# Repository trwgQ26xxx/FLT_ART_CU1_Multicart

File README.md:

# Multicart ROM module for Fiat Lancia Tester \ Alfa Romeo Tester \ Check Up 1

A multicart ROM module that replaces eight standard FLT modules. It contains eight ROM sets stored in a 512kB (4Mbit) flash memory, which can be switched on the fly.

Two variants are implemented: one using an Atmel AT89C2051 MCU (revisions A - green and B - blue), and another based on a Microchip ATtiny806 (revision C - yellow).

# Disclaimer

I do not consent to the use of all or part of the project for commercial purposes!

Nie wyrażam zgody na wykorzystanie całości bądź części projektu w celach zarobkowych!

# License

Shield: [![CC BY-NC-SA 4.0][cc-by-nc-sa-shield]][cc-by-nc-sa]

This work is licensed under a
[Creative Commons Attribution-NonCommercial-ShareAlike 4.0 International License][cc-by-nc-sa].

[![CC BY-NC-SA 4.0][cc-by-nc-sa-image]][cc-by-nc-sa]

[cc-by-nc-sa]: http://creativecommons.org/licenses/by-nc-sa/4.0/
[cc-by-nc-sa-image]: https://licensebuttons.net/l/by-nc-sa/4.0/88x31.png
[cc-by-nc-sa-shield]: https://img.shields.io/badge/License-CC%20BY--NC--SA%204.0-lightgrey.svg

# Directories organization

- **firmware** - MCU firmware written in C, provided for both the AT89C2051 and ATtiny806 variants.
- **merge** - A script that automatically combines up to eight modules into a single package suitable for loading onto the multicart.
- **PCB** - KiCad PCB project files, available for both the AT89C2051 and ATtiny806 hardware revisions.
- **DS** - Datasheets for all components used in the project.

# Instructions

Switching modules (ROMs) is accomplished by pressing the BACK and NEXT keys. With each press, a dot lights up on the display for the FLT reset time (approximately 200 ms). The display indicates the number of the currently running module.

The FLASH memories used, of 39SF040 type (or equivalent), have a capacity of 512kB. Considering that the largest FLT modules ROMs are 64kB, I designed the multicart's capacity to accomodate 8 modules.

# ROMS preparation

The FLASH memory contents can be changed according to the following principles.

**ROM index** | **Base offset**
:---: | :---:
1 | 0x00000
2 | 0x10000
3 | 0x20000
4 | 0x30000
5 | 0x40000
6 | 0x50000
7 | 0x60000
8 | 0x70000

Let's assume we want to load the module at index 3, for which the base offset is 0x20000.

**ROM** | **SIZE** | **The ROM given is PRESENT in the module being loaded at index 3** | **The ROM given is NOT PRESENT in the module being loaded at index 3**
:---: | :---: | :---: | :---:
A | 8kB | Load the content of ROM A into FLASH memory A addresses 0x20000-0x21FFF.Fill addresses 0x22000-0x2FFFF of FLASH memory A with 0xFF. | Fill addresses 0x20000-0x2FFFF of FLASH memory A with 0xFF.
B | 32kB | Load the content of ROM B into FLASH memory B addresses 0x28000-0x2FFFF. Fill addresses 0x20000-0x27FFF of FLASH memory B with 0xFF. | ROM B is always present.
B | 64kB | Load the content of ROM B into FLASH memory B addresses 0x20000-0x2FFFF. | ROM B is always present.
C | 32kB | Load the content of ROM C into FLASH memory C addresses 0x28000-0x2FFFF. Fill addresses 0x20000-0x27FFF of FLASH memory C with 0xFF. | Fill addresses 0x20000-0x2FFFF of FLASH memory C with 0xFF.
C | 64kB | Load the content of ROM C into FLASH memory C addresses 0x20000-0x2FFFF. | Fill addresses 0x20000-0x2FFFF of FLASH memory C with 0xFF.

It should be noted here that the utilization of FLASH memory A is at most 12.5%, as only 8kB of each 64kB bank is utilized. However, I opted for this solution to simplify the process of preparing Flash memory content, given the use of identical offsets.

# Notes

- Use the APX810-40SA as the reset supervisor for the AT89C2051 MCU (U7 on the PCB) in revisions A and B.

- Wiring the MPLAB ICD5 8P8C Connector to the Multicart PROG Connector (Revision C):

**SIGNAL** | **PROG pin** | **8P8C pin**
:---: | :---: | :---:
GND | 1 | 5
UPDI | 2 | 4
VCC | 3 | 6

- 0.28" LED displays are available in two pinout variants. The first variant uses common pins 1 and 6. The second variant uses common pins 3 and 8. **Revisions B and C of the project require the display with common pins 3 and 8.** The version with common pins 1 and 6 was used only in revision A.

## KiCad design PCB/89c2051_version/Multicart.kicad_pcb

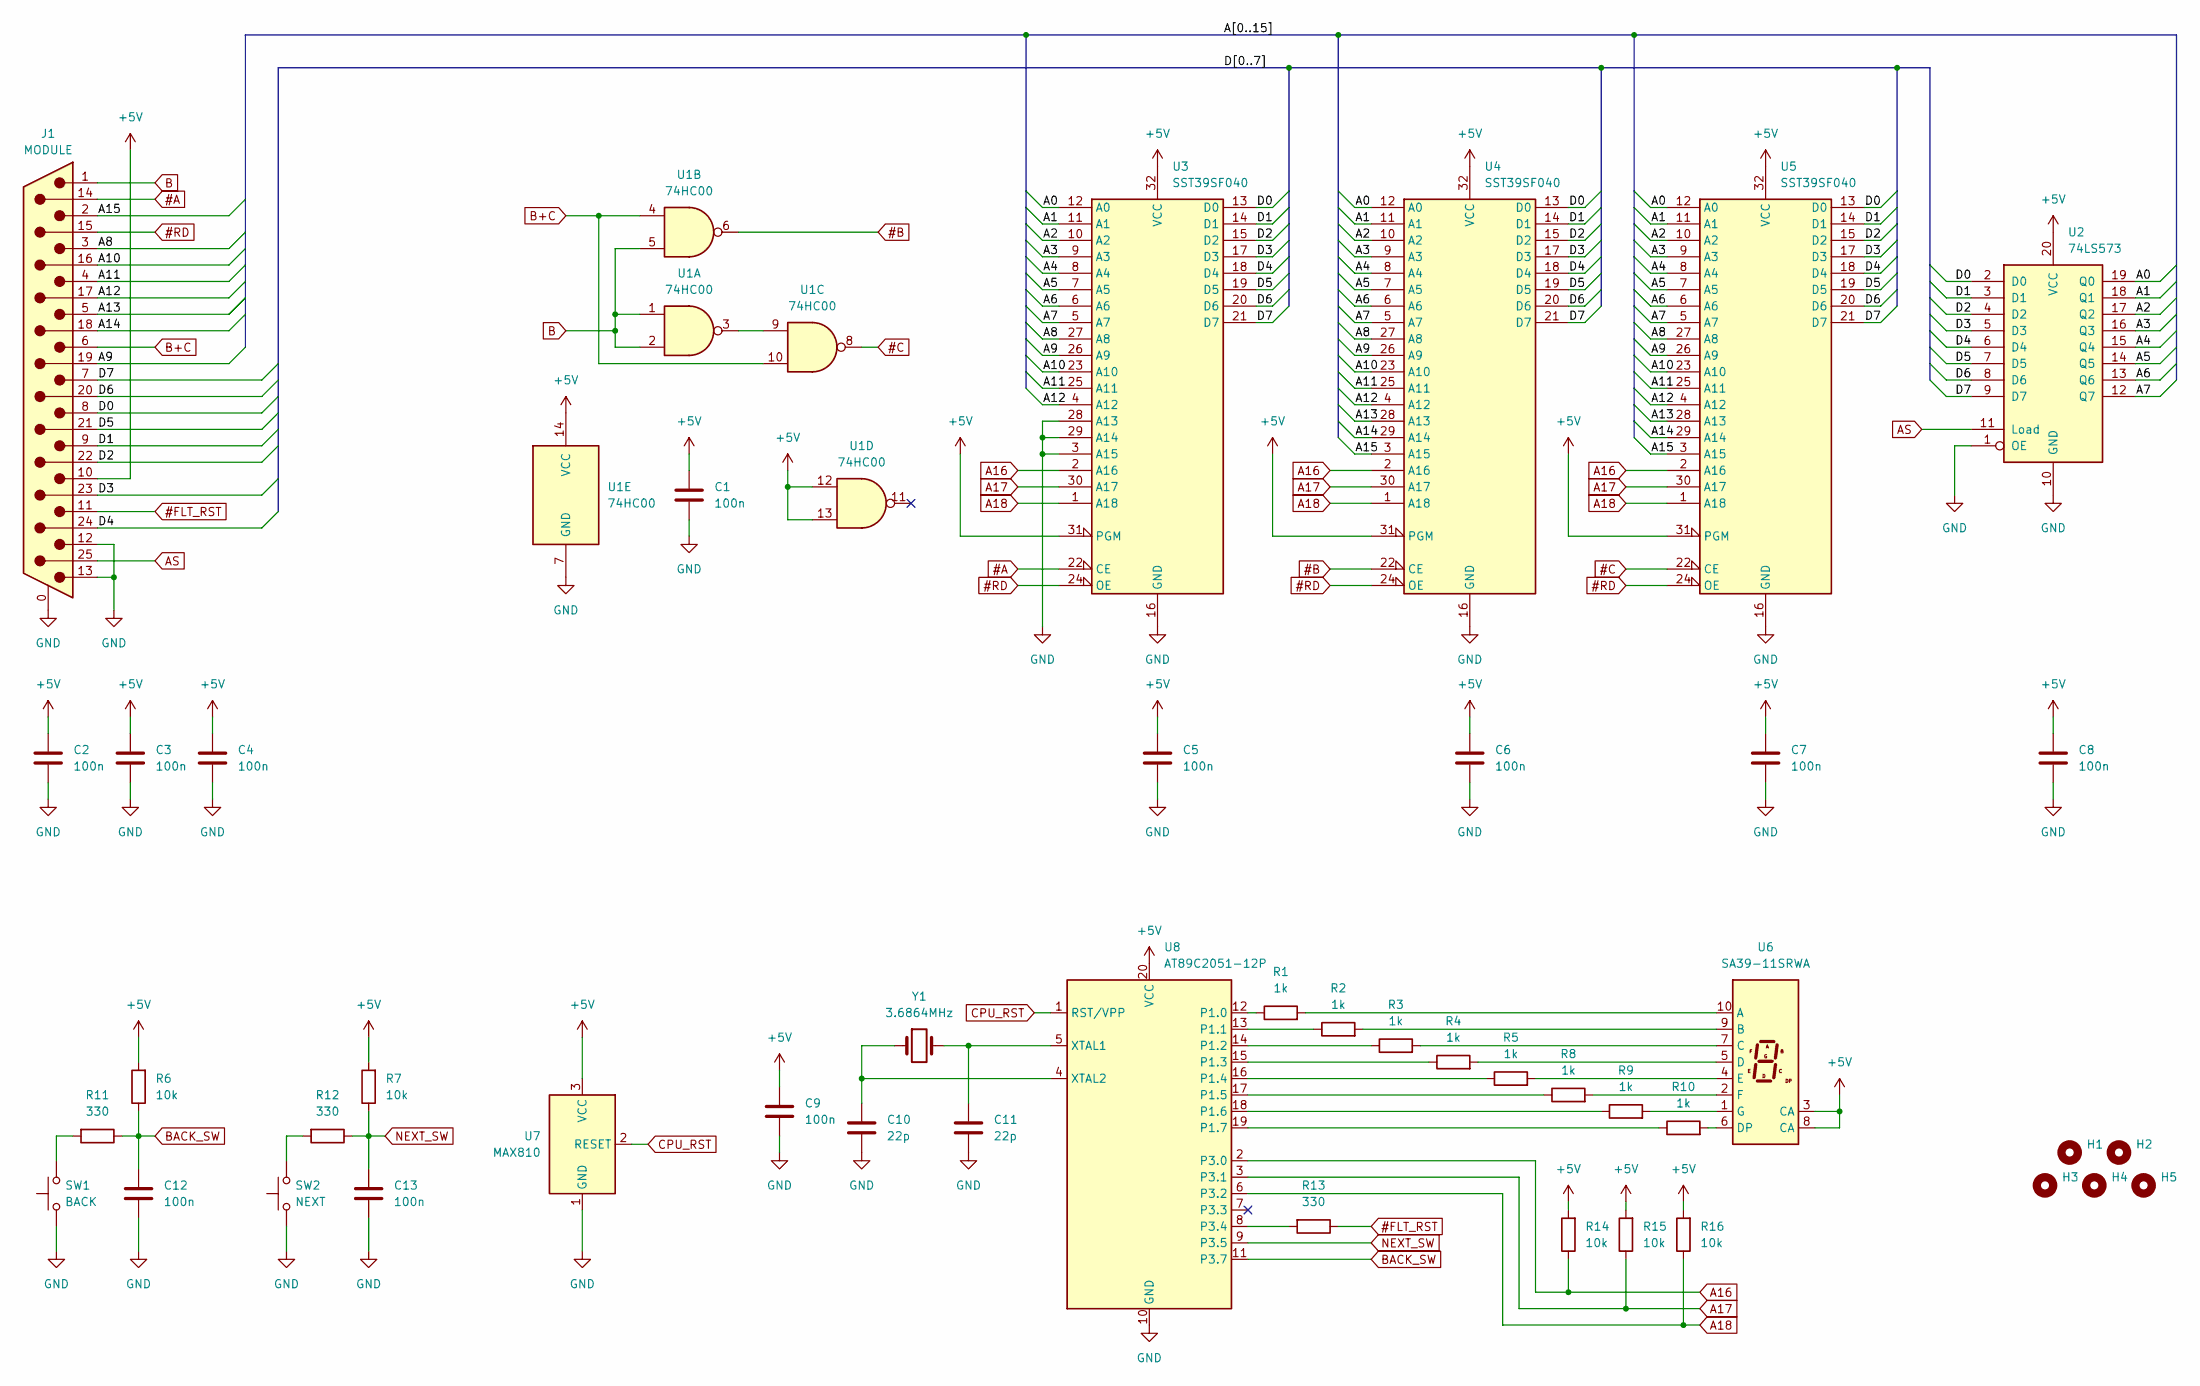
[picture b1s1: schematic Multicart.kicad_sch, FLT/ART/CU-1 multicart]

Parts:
C1, C2, C3, C4, C5, C6, C7, C8, C9, C12, C13: 100n; C_1206_3216Metric_Pad1.33x1.80mm_HandSolder
C10, C11: 22p; C_1206_3216Metric_Pad1.33x1.80mm_HandSolder
H1, H2, H3, H4, H5: MountingHole_3.2mm_M3_DIN965
J1: MODULE; DSUB-25_Male_Horizontal_P2.77x2.84mm_EdgePinOffset4.94mm_Ho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
R1, R2, R3, R4, R5, R8, R9, R10: 1k; R_1206_3216Metric_Pad1.30x1.75mm_HandSolder
R6, R7, R14, R15, R16: 10k; R_1206_3216Metric_Pad1.30x1.75mm_HandSolder
R11, R12, R13: 330; R_1206_3216Metric_Pad1.30x1.75mm_HandSolder
SW1: BACK; SW_PUSH_6mm
SW2: NEXT; SW_PUSH_6mm
U1: 74HC00; SOIC-14_3.9x8.7mm_P1.27mm
U2: 74LS573; SOIC-20W_7.5x12.8mm_P1.27mm
U3, U4, U5: SST39SF040; PLCC-32_11.4x14.0mm_P1.27mm
U6: SA39-11SRWA; Sx39-1xxxxx
U7: MAX810; SOT-23
U8: AT89C2051-12P; DIP-20_W7.62mm
Y1: 3.6864MHz; Crystal_HC49-4H_Vertical

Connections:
#A: J1.14, U3.22 (CE)
#B: U1.6, U4.22 (CE)
#C: U1.8, U5.22 (CE)
#FLT_RST: J1.11, R13.1
#RD: J1.15, U3.24 (OE), U4.24 (OE), U5.24 (OE)
+5V: C1.1, C2.1, C3.1, C4.1, C5.1, C6.1, C7.1, C8.1, C9.1, J1.10, R6.2, R7.2, R14.2, R15.2, R16.2, U1.12, U1.13, U1.14 (VCC), U2.20 (VCC), U3.31 (PGM), U3.32 (VCC), U4.31 (PGM), U4.32 (VCC), U5.31 (PGM), U5.32 (VCC), U6.3 (CA), U6.8 (CA), U7.3 (VCC), U8.20 (VCC)
/A0: U2.19 (Q0), U3.12 (A0), U4.12 (A0), U5.12 (A0)
/A1: U2.18 (Q1), U3.11 (A1), U4.11 (A1), U5.11 (A1)
/A2: U2.17 (Q2), U3.10 (A2), U4.10 (A2), U5.10 (A2)
/A3: U2.16 (Q3), U3.9 (A3), U4.9 (A3), U5.9 (A3)
/A4: U2.15 (Q4), U3.8 (A4), U4.8 (A4), U5.8 (A4)
/A5: U2.14 (Q5), U3.7 (A5), U4.7 (A5), U5.7 (A5)
/A6: U2.13 (Q6), U3.6 (A6), U4.6 (A6), U5.6 (A6)
/A7: U2.12 (Q7), U3.5 (A7), U4.5 (A7), U5.5 (A7)
/A8: J1.3, U3.27 (A8), U4.27 (A8), U5.27 (A8)
/A9: J1.19, U3.26 (A9), U4.26 (A9), U5.26 (A9)
/A10: J1.16, U3.23 (A10), U4.23 (A10), U5.23 (A10)
/A11: J1.4, U3.25 (A11), U4.25 (A11), U5.25 (A11)
/A12: J1.17, U3.4 (A12), U4.4 (A12), U5.4 (A12)
/A13: J1.5, U4.28 (A13), U5.28 (A13)
/A14: J1.18, U4.29 (A14), U5.29 (A14)
/A15: J1.2, U4.3 (A15), U5.3 (A15)
/D0: J1.8, U2.2 (D0), U3.13 (D0), U4.13 (D0), U5.13 (D0)
/D1: J1.9, U2.3 (D1), U3.14 (D1), U4.14 (D1), U5.14 (D1)
/D2: J1.22, U2.4 (D2), U3.15 (D2), U4.15 (D2), U5.15 (D2)
/D3: J1.23, U2.5 (D3), U3.17 (D3), U4.17 (D3), U5.17 (D3)
/D4: J1.24, U2.6 (D4), U3.18 (D4), U4.18 (D4), U5.18 (D4)
/D5: J1.21, U2.7 (D5), U3.19 (D5), U4.19 (D5), U5.19 (D5)
/D6: J1.20, U2.8 (D6), U3.20 (D6), U4.20 (D6), U5.20 (D6)
/D7: J1.7, U2.9 (D7), U3.21 (D7), U4.21 (D7), U5.21 (D7)
A16: R14.1, U3.2 (A16), U4.2 (A16), U5.2 (A16), U8.2 (P3.0)
A17: R15.1, U3.30 (A17), U4.30 (A17), U5.30 (A17), U8.3 (P3.1)
A18: R16.1, U3.1 (A18), U4.1 (A18), U5.1 (A18), U8.6 (P3.2)
AS: J1.25, U2.11 (Load)
B: J1.1, U1.1, U1.2, U1.5
B+C: J1.6, U1.4, U1.10
BACK_SW: C12.1, R6.1, R11.1, U8.11 (P3.7)
CPU_RST: U7.2 (RESET), U8.1 (RST/VPP)
GND: C1.2, C2.2, C3.2, C4.2, C5.2, C6.2, C7.2, C8.2, C9.2, C10.2, C11.2, C12.2, C13.2, J1.0, J1.12, J1.13, SW1.1, SW2.1, U1.7 (GND), U2.1 (OE), U2.10 (GND), U3.3 (A15), U3.16 (GND), U3.28 (A13), U3.29 (A14), U4.16 (GND), U5.16 (GND), U7.1 (GND), U8.10 (GND)
NEXT_SW: C13.1, R7.1, R12.1, U8.9 (P3.5)
unnamed: R11.2, SW1.2
unnamed: R12.2, SW2.2
unnamed: U1.3, U1.9
unnamed: R1.2, U6.10 (A)
unnamed: R2.2, U6.9 (B)
unnamed: R3.2, U6.7 (C)
unnamed: R4.2, U6.5 (D)
unnamed: R10.2, U6.6 (DP)
unnamed: R5.2, U6.4 (E)
unnamed: R8.2, U6.2 (F)
unnamed: R9.2, U6.1 (G)
unnamed: R1.1, U8.12 (P1.0)
unnamed: R2.1, U8.13 (P1.1)
unnamed: R3.1, U8.14 (P1.2)
unnamed: R4.1, U8.15 (P1.3)
unnamed: R5.1, U8.16 (P1.4)
unnamed: R8.1, U8.17 (P1.5)
unnamed: R9.1, U8.18 (P1.6)
unnamed: R10.1, U8.19 (P1.7)
unnamed: R13.2, U8.8 (P3.4)
unnamed: C11.1, U8.5 (XTAL1), Y1.2
unnamed: C10.1, U8.4 (XTAL2), Y1.1

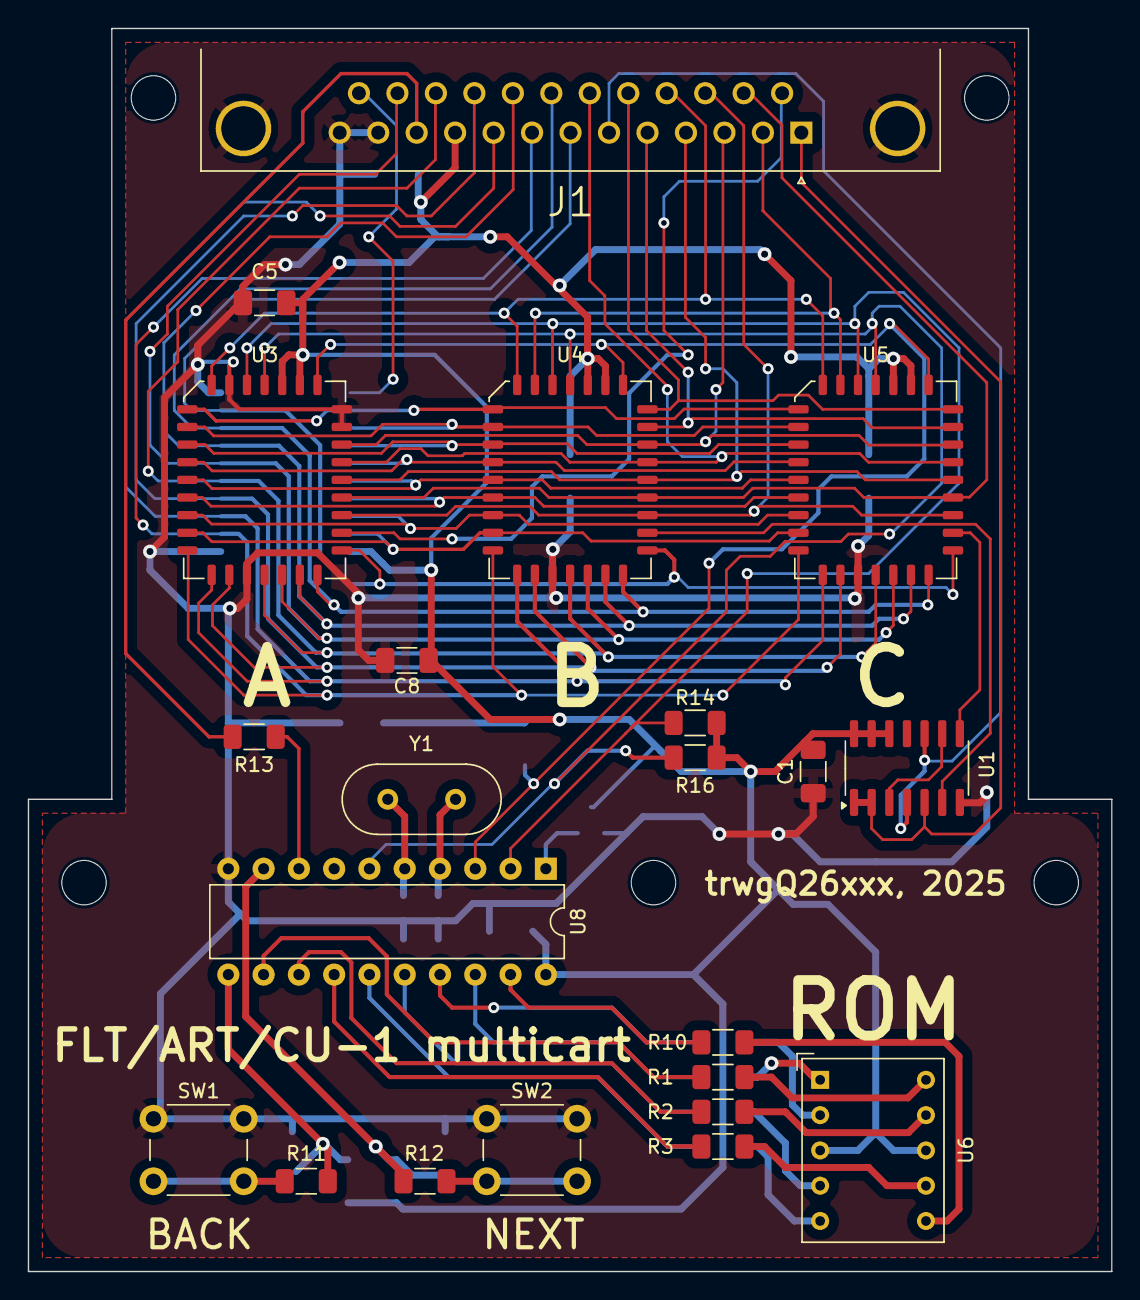
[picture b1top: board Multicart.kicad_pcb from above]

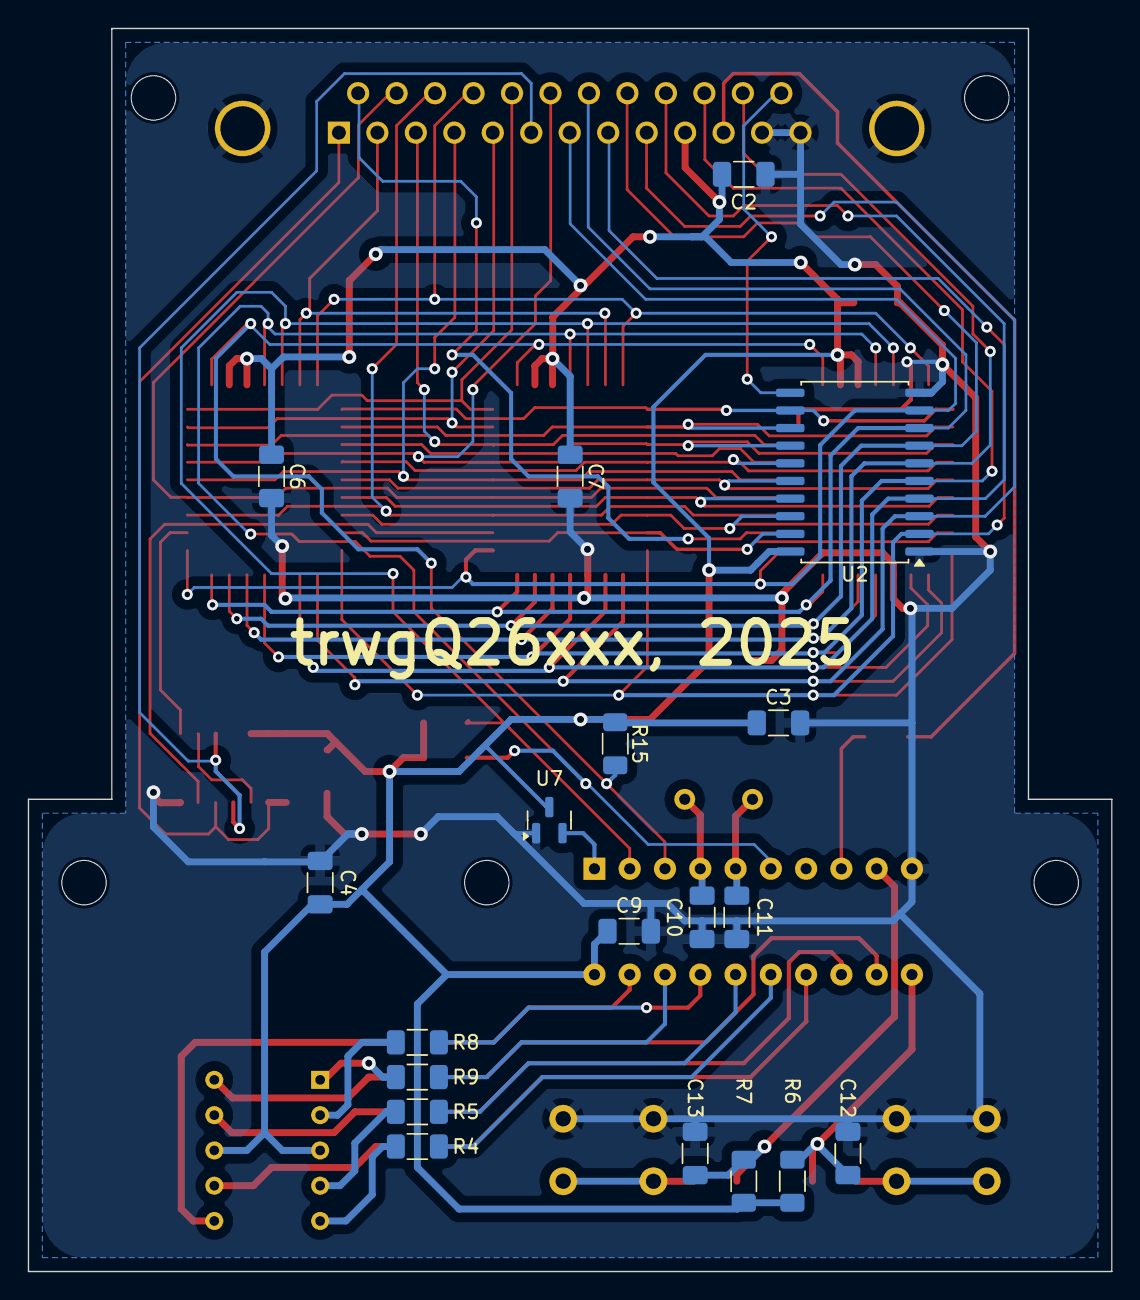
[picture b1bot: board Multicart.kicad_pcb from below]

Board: 2 copper layers, 78.0 x 89.5 mm, 46 parts (19 on the bottom side), 62 nets.

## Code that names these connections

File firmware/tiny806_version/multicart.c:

/*
Project name:	FLT/CU1 multicart
Author: 		trwgQ26xxx
Date:			25.02.2026
Target MCUs:	Attiny 406/806
Compiler:		AVR_8_bit_GNU_Toolchain_4.0.0_52), Microchip.ATtiny_DFP.3.3.272
*/

#include <stdint.h>
#include <stdbool.h>

#include <avr/io.h>
#include <avr/interrupt.h>
#include <avr/wdt.h>
#include <avr/fuse.h>

/*
------------------ CONNECTIONS ------------------

7 segment display:
PA5 - PA7 => A, B, C; PB2 - PB5 => D, E, G, F; PA4 = DP

Flash memory address lines:
PC0 - PC2 => A16 - A18; PC3 = NC (A19 - FFU)

FLT reset:
PB0 = #FLT_RST

Push buttons:
PA3 = NEXT_SW, PA2 = BACK_SW

------------------ CONNECTIONS ------------------
*/

#define NUMBER_OF_BANKS	8

#define F_TIMER			(F_CPU / 256)					/* Hz, for TCA0 with DIV256 prescaler */
#define KEYB_DELAY		200								/* ms */
#define TIMER_VAL		((KEYB_DELAY * F_TIMER) / 1000)	/* ticks */
#define TIMER_VAL_MAX	0xFFFF							/* Max value for 16-bit timer */

#if (TIMER_VAL > TIMER_VAL_MAX)
	#error "Set keyboard delay is larger than maximum possible"
#endif

#define NEXT_KEY_IS_PRESSED				(!(PORTA.IN & (1 << 3)))
#define BACK_KEY_IS_PRESSED				(!(PORTA.IN & (1 << 2)))
#define ALL_KEYS_ARE_RELEASED			((PORTA.IN & (1 << 3)) && (PORTA.IN & (1 << 2)))

/* DIGITS: 1 - 8 */
volatile const unsigned char led_codes[NUMBER_OF_BANKS] = {0x06, 0x3B, 0x2F, 0x66, 0x6D, 0x7D, 0x07, 0x7F};

volatile bool keyboard_locked = false;
volatile uint8_t current_mem_bank = 0;

static void Run_FLT(bool run);
static void Change_mem_bank(uint8_t bank);
static void Update_LED_Display(uint8_t digit, bool dot_status);

static void Start_Timer(void);
static void Switch_Bank(void);

int main(void)
{
	/* Poke WDT */
	wdt_reset();

	/* FUSE set to 16MHz, enable 16 prescaler so F_CPU is 1MHz */
	_PROTECTED_WRITE(CLKCTRL.MCLKCTRLB, CLKCTRL_PDIV_16X_gc | CLKCTRL_PEN_bm);

	/* Initialize timer */
	TCA0.SINGLE.CTRLA = TCA_SINGLE_CLKSEL_DIV256_gc;	/* Set prescaler to 256 */
	TCA0.SINGLE.CTRLB = TCA_SINGLE_WGMODE_NORMAL_gc;	/* Set normal mode */
	TCA0.SINGLE.CTRLC = 0;								/* No compare channels */
	TCA0.SINGLE.CTRLD = 0;								/* No split mode */
	TCA0.SINGLE.CTRLECLR = TCA_SINGLE_DIR_bm;			/* Clear direction bit (count up mode) */
	TCA0.SINGLE.EVCTRL = 0;								/* No event control */
	TCA0.SINGLE.PER = TIMER_VAL;						/* Set period for desired delay */
	TCA0.SINGLE.CNT = 0;								/* Clear counter */

	TCA0.SINGLE.INTFLAGS = TCA_SINGLE_OVF_bm;			/* Clear interrupt flag */
	TCA0.SINGLE.INTCTRL = TCA_SINGLE_OVF_bm;			/* Enable overflow interrupt */

	/* Initialize memory bank switch output */
	PORTC.DIRSET = 0x0F;
	PORTC.OUTCLR = 0x0F;								/* Set to first bank */

	/* Initialize FLT reset output */
	PORTB.DIRSET = (1 << 0);
	PORTB.OUTSET = (1 << 0);							/* Hold in reset */

	/* Initialize display */
	PORTA.DIRSET = 0xF0; PORTB.DIRSET = 0x3C;
	PORTA.OUTSET = 0xF0; PORTB.OUTSET = 0x3C;			/* LED display off */

	/* Initialize keyboard inputs */
	PORTA.DIRCLR = (1 << 3) | (1 << 2);
	PORTA.PIN2CTRL = PORT_PULLUPEN_bm;					/* Enable pull-up on PA2 (BACK_SW) */
	PORTA.PIN3CTRL = PORT_PULLUPEN_bm;					/* Enable pull-up on PA3 (NEXT_SW) */

	/* Configure unused pins */
	PORTA.DIRCLR = (1 << 1) | (1 << 0);					/* Configure PA0 and PA1 as inputs */
	PORTA.PIN0CTRL = PORT_PULLUPEN_bm;					/* Enable pull-up on PA0 */
	PORTA.PIN1CTRL = PORT_PULLUPEN_bm;					/* Enable pull-up on PA1 */
	PORTB.DIRCLR = (1 << 1);							/* Configure PB1 as input */
	PORTB.PIN1CTRL = PORT_PULLUPEN_bm;					/* Enable pull-up on PB1 */

	/* Init variables */
	current_mem_bank = 0;
	keyboard_locked = true;

	/* Enable interrupts globally */
	sei();

	/* Do one transaction on start */
	Switch_Bank();

	while(true)
	{
		/* If keyboard is unlocked */
		if(keyboard_locked == false)
		{
			/* Check NEXT key */
			if(NEXT_KEY_IS_PRESSED)
			{
				/* If pressed, advance bank forward */
				if(current_mem_bank >= (NUMBER_OF_BANKS - 1))
				{
					current_mem_bank = 0;
				}
				else
				{
					current_mem_bank++;
				}

				Switch_Bank();
			}
			/* Check BACK key */
			else if(BACK_KEY_IS_PRESSED)
			{
				/* If pressed, advance bank backward */
				if(current_mem_bank == 0)
				{
					current_mem_bank = NUMBER_OF_BANKS - 1;
				}
				else
				{
					current_mem_bank--;
				}

				Switch_Bank();
			}
		}

		/* Poke WDT */
		wdt_reset();
	}
}

ISR(TCA0_OVF_vect)
{
	/* Kill timer */
	TCA0.SINGLE.CTRLA &= ~TCA_SINGLE_ENABLE_bm;

	/* Clear IRQ flag */
	TCA0.SINGLE.INTFLAGS = TCA_SINGLE_OVF_bm;

	/* Run FLT */
	Run_FLT(true);

	/* Update display, hide dot */
	Update_LED_Display(current_mem_bank, false);

	/* Check if all keys are released */
	if(ALL_KEYS_ARE_RELEASED)
	{
		/* Unlock keyboard */
		keyboard_locked = false;
	}
	else
	{
		/* Waiting for buttons to be released, restart timer */
		Start_Timer();
	}
}

static void Start_Timer(void)
{
	/* Kill timer */
	TCA0.SINGLE.CTRLA &= ~TCA_SINGLE_ENABLE_bm;

	/* Clear timer */
	TCA0.SINGLE.CNT = 0;

	/* Clear IRQ flag */
	TCA0.SINGLE.INTFLAGS = TCA_SINGLE_OVF_bm;

	/* Start timer */
	TCA0.SINGLE.CTRLA |= TCA_SINGLE_ENABLE_bm;
}

static void Switch_Bank(void)
{
	/* Lock keyboard */
	keyboard_locked = true;

	/* Halt FLT */
	Run_FLT(false);

	/* Switch bank */
	Change_mem_bank(current_mem_bank);

	/* Update display, show dot */
	Update_LED_Display(current_mem_bank, true);

	/* Start timer */
	Start_Timer();
}

static void Run_FLT(bool run)
{
	/* Set FLT control pin */
	if(run == true)
		PORTB.OUTSET = (1 << 0);
	else
		PORTB.OUTCLR = (1 << 0);
}

static void Change_mem_bank(uint8_t bank)
{
	/* Change memory bank */
	PORTC.OUTCLR = 0x0F;
	PORTC.OUTSET = (bank & 0x0F);
}

static void Update_LED_Display(uint8_t digit, bool dot_status)
{
	/* Check if digit is within range */
	if(digit >= NUMBER_OF_BANKS)
		digit = 0;

	/* Clear display */
	PORTA.OUTSET = 0xE0;
	PORTB.OUTSET = 0x3C;

	/* Update digit */
	PORTA.OUTCLR = (led_codes[digit] & 0x07) << 5;
	PORTB.OUTCLR = (led_codes[digit] & 0x78) >> 1; // ((led_codes[digit] & 0x78) >> 3) << 2

	/* Update dot */
	if(dot_status == true)
		PORTA.OUTCLR = (1 << 4);
	else
		PORTA.OUTSET = (1 << 4);
}

/* FUSE configuration */
FUSES = {
	.WDTCFG  = 0x06,	/* Watchdog: Timeout = 256CLK (0.256s), Window mode off */
	.BODCFG  = 0xF5,	/* BOD: Level = 4.2V, Sample Frequency = 125Hz, Enabled mode in active & sleep */
	.OSCCFG  = 0x01,	/* Internal 16MHz RC Oscillator, calibration registers unlocked */
	.SYSCFG0 = 0xF2,	/* No CRC, Reset/UPDI pin configured as GPIO, EEPROM erased during chip erase */
	.SYSCFG1 = 0x04,	/* Start-Up Time = 8ms */
	.APPEND  = 0x00,	/* Application Code Section End, unused */
	.BOOTEND = 0x00		/* Boot Section End, unused */
};

/* LOCKBIT configuration */
LOCKBITS = 0xC5;		/* Memory access is unlocked */

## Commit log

2024-04-20 AT89C2051 firmware prepared
2024-04-20 Compile script & output file added
2024-04-20 README updated
2024-04-20 Datasheets added
2024-04-20 PCB project added
2024-04-20 Schematic in PDF added
2024-04-20 Preview image added
2024-04-20 Preview added
2024-04-23 LED display fix
2024-04-23 Show digit code on LCD instead of binary number
2024-04-23 Keyboard delay changed to 100ms
2024-04-23 Change FLT #RST logic, increase delay to 210ms
2024-04-26 Cosmetic change: compilation error is shown when set delay exceeds maximum
2024-06-26 README.md updated
2024-06-27 Replaced render with actual photos
2024-08-24 License information added
2025-01-22 Updated .gitignore
2025-01-22 Added 29C020 datasheet
2025-05-07 Added a merge script that automatically merges up to 8 modules into a single package, loadable onto a multicart
2025-10-15 Added SDCC with manual
2025-12-20 PCB updated, B will be the last revision to use 89C2051
2025-12-20 Update for production
2026-01-25 MCU changed to Attiny 406/806, PCB updated to revision C
2026-02-08 Last PCB update before production
2026-02-08 Added 8k ROM case to merge script
2026-03-08 Added code for ATtiny806 version
2026-03-08 PCB directory splitted for two (89C2051 and ATtiny806) versions
2026-03-09 README updated, added more photos
2026-04-11 Photos updated
2026-04-11 AVR-GCC optimization analysis added
